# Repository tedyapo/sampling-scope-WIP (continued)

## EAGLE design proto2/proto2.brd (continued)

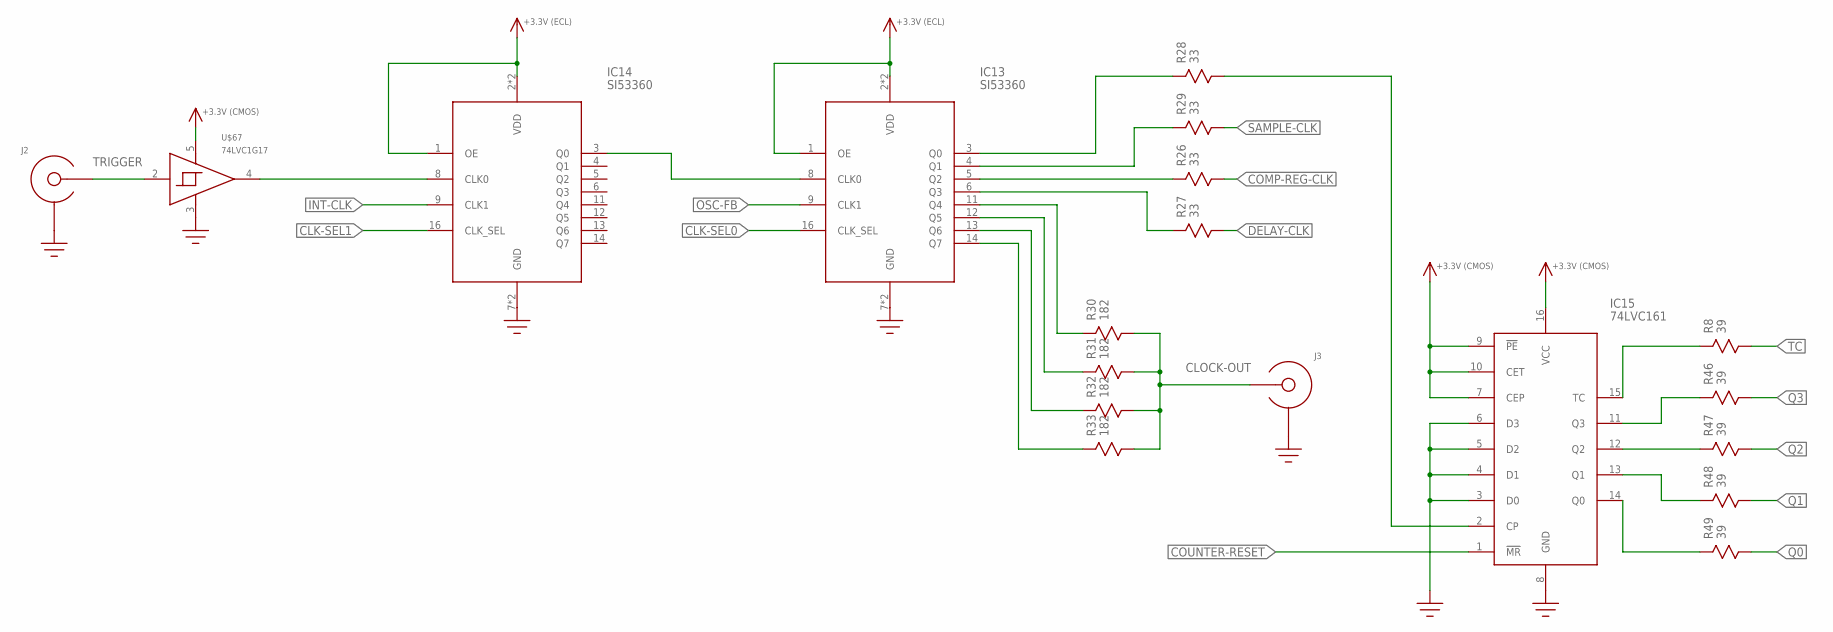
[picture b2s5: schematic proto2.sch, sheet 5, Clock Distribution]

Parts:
IC13, IC14: SI53360; TSSOP16
IC15: 74LVC161; SOIC-16
J2, J3: SMA-EDGE-LAUNCH4L-4020-TAPER-FIXED; SMA_EDGE_LAUNCH_4L_4020_TAPER_FIXED
R8, R46, R47, R48, R49: 39; 0402
R26, R27, R28, R29: 33; R0603
R30, R31, R32, R33: 182; R0603
U$67: 74LVC1G17; SOT23-5

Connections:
CLK-SEL0: IC13.16 (CLK_SEL); also elsewhere on the board
CLK-SEL1: IC14.16 (CLK_SEL); also elsewhere on the board
CLOCK-OUT: J3.CENTER@1 (CENTER), J3.P$3 (CENTER), R30.P$2, R31.P$2, R32.P$2, R33.P$2
COMP-REG-CLK: R26.P$2; also elsewhere on the board
COUNTER-RESET: IC15.1 (!MR!); also elsewhere on the board
DELAY-CLK: R27.P$2; also elsewhere on the board
GND: IC13.7 (GND), IC13.10 (GND), IC14.7 (GND), IC14.10 (GND), IC15.3 (D0), IC15.4 (D1), IC15.5 (D2), IC15.6 (D3), IC15.8 (GND), J2.BOTTOM_GND (SHIELD), J2.GND@1 (SHIELD), J2.GND@2 (SHIELD), J2.GND@3 (SHIELD), J2.GND@4 (SHIELD), J2.GND@5 (SHIELD), J2.GND@6 (SHIELD), J2.GND@7 (SHIELD), J2.GND@8 (SHIELD), J2.GND@14 (SHIELD), J2.GND@15 (SHIELD), J2.GND@16 (SHIELD), J2.GND@17 (SHIELD), J2.GND_PAD1 (SHIELD), J2.GND_PAD2 (SHIELD), J2.P$1 (SHIELD), J2.P$2 (SHIELD), J3.BOTTOM_GND (SHIELD), J3.GND@1 (SHIELD), J3.GND@2 (SHIELD), J3.GND@3 (SHIELD), J3.GND@4 (SHIELD), J3.GND@5 (SHIELD), J3.GND@6 (SHIELD), J3.GND@7 (SHIELD), J3.GND@8 (SHIELD), J3.GND@14 (SHIELD), J3.GND@15 (SHIELD), J3.GND@16 (SHIELD), J3.GND@17 (SHIELD), J3.GND_PAD1 (SHIELD), J3.GND_PAD2 (SHIELD), J3.P$1 (SHIELD), J3.P$2 (SHIELD), U$67.3 (GND); also elsewhere on the board
INT-CLK: IC14.9 (CLK1); also elsewhere on the board
unnamed: IC15.12 (Q2), R47.1
unnamed: IC13.5 (Q2), R26.P$1
unnamed: IC13.6 (Q3), R27.P$1
unnamed: IC13.4 (Q1), R29.P$1
unnamed: IC14.8 (CLK0), U$67.4 (OUT)
unnamed: IC13.8 (CLK0), IC14.3 (Q0)
unnamed: IC13.3 (Q0), R28.P$1
unnamed: IC15.2 (CP), R28.P$2
unnamed: IC13.11 (Q4), R30.P$1
unnamed: IC13.12 (Q5), R31.P$1
unnamed: IC13.13 (Q6), R32.P$1
unnamed: IC13.14 (Q7), R33.P$1
unnamed: IC15.11 (Q3), R46.1
unnamed: IC15.15 (TC), R8.1
unnamed: IC15.13 (Q1), R48.1
unnamed: IC15.14 (Q0), R49.1
OSC-FB: IC13.9 (CLK1); also elsewhere on the board
Q0: R49.2; also elsewhere on the board
Q1: R48.2; also elsewhere on the board
Q2: R47.2; also elsewhere on the board
Q3: R46.2; also elsewhere on the board
SAMPLE-CLK: R29.P$2; also elsewhere on the board
TC: R8.2; also elsewhere on the board
TRIGGER: J2.CENTER@1 (CENTER), J2.P$3 (CENTER), U$67.2 (IN)
VCC1: IC13.1 (OE), IC13.2 (VDD), IC13.15 (VDD), IC14.1 (OE), IC14.2 (VDD), IC14.15 (VDD); also elsewhere on the board
VCC2: IC15.7 (CEP), IC15.9 (!PE!), IC15.10 (CET), IC15.16 (VCC), U$67.5 (VCC); also elsewhere on the board

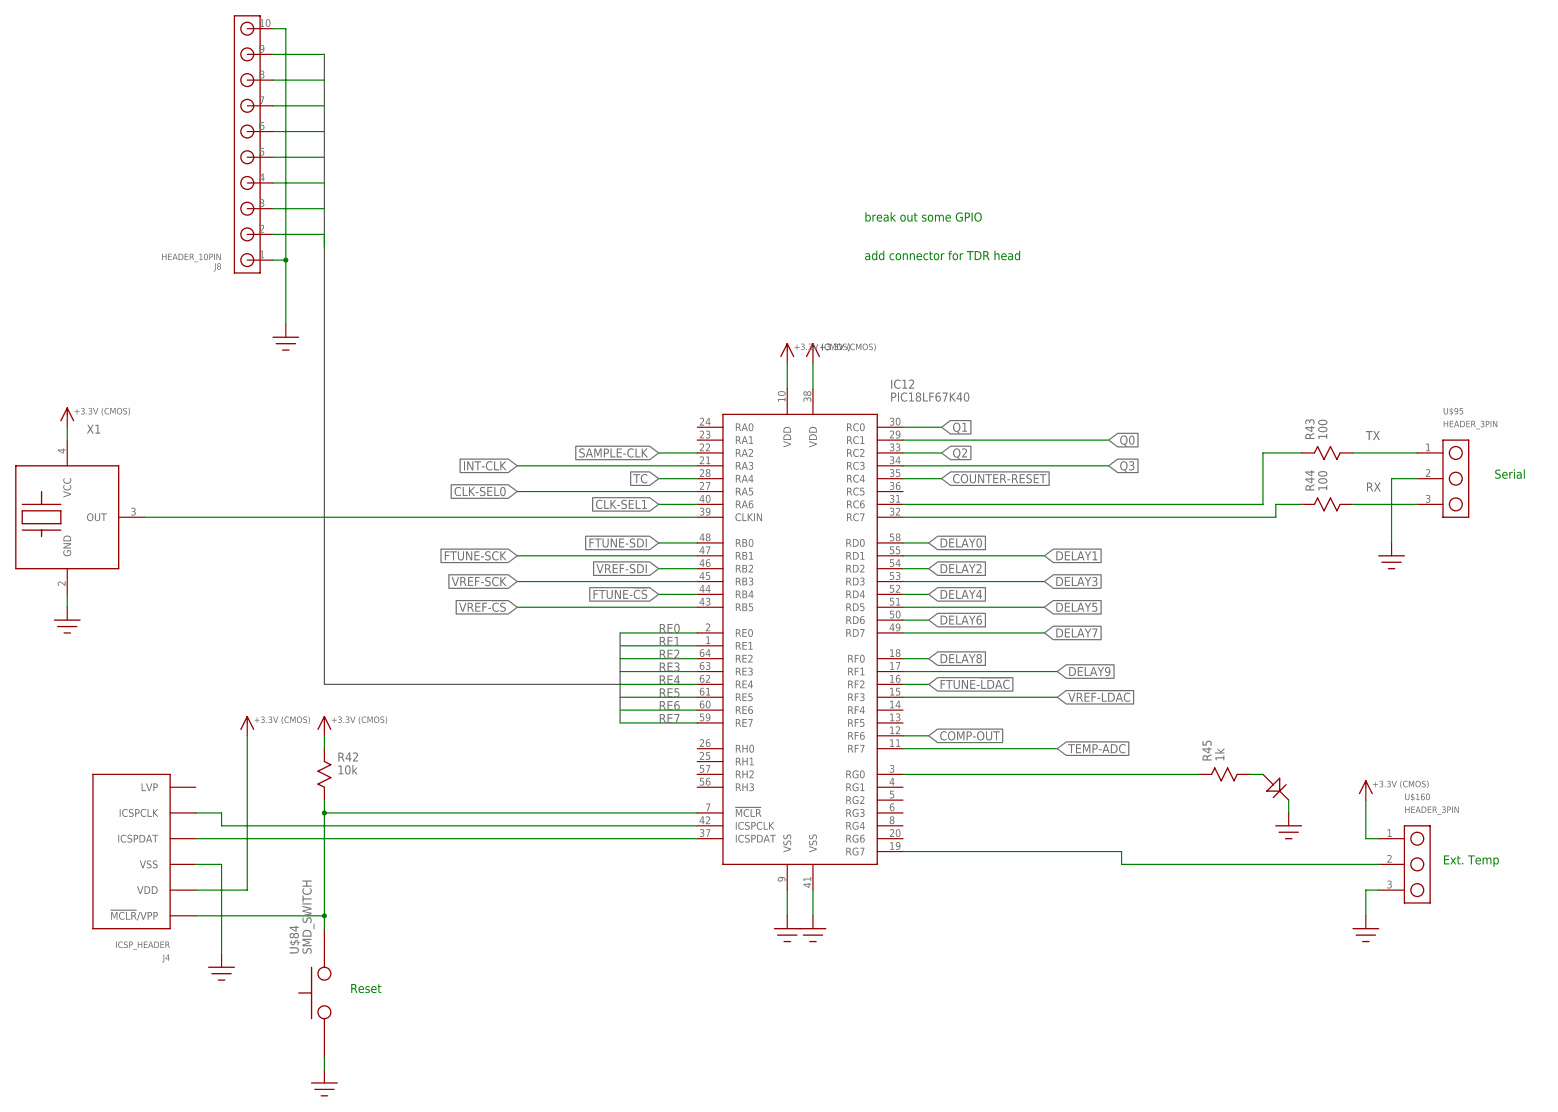
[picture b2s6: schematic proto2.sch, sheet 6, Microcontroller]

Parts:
IC12: PIC18LF67K40; TQFP-100-10X10
J4: ICSP_HEADER; HEADER_6PIN
J8: HEADER_10PIN
R42: 10k; R0603
R43, R44: 100; R0603
R45: 1k; R0603
U$84: SMD_SWITCH
U$95, U$160: HEADER_3PIN
U$97: LED_0603
X1: XTAL_OSC; XTAL_3.2X5

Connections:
CLK-SEL0: IC12.27 (RA5); also elsewhere on the board
CLK-SEL1: IC12.40 (RA6); also elsewhere on the board
COMP-OUT: IC12.12 (RF6); also elsewhere on the board
COUNTER-RESET: IC12.35 (RC4); also elsewhere on the board
DELAY0: IC12.58 (RD0); also elsewhere on the board
DELAY1: IC12.55 (RD1); also elsewhere on the board
DELAY2: IC12.54 (RD2); also elsewhere on the board
DELAY3: IC12.53 (RD3); also elsewhere on the board
DELAY4: IC12.52 (RD4); also elsewhere on the board
DELAY5: IC12.51 (RD5); also elsewhere on the board
DELAY6: IC12.50 (RD6); also elsewhere on the board
DELAY7: IC12.49 (RD7); also elsewhere on the board
DELAY8: IC12.18 (RF0); also elsewhere on the board
DELAY9: IC12.17 (RF1); also elsewhere on the board
FTUNE-!CS!: IC12.44 (RB4); also elsewhere on the board
FTUNE-!LDAC!: IC12.16 (RF2); also elsewhere on the board
FTUNE-SCK: IC12.47 (RB1); also elsewhere on the board
FTUNE-SDI: IC12.48 (RB0); also elsewhere on the board
GND: IC12.9 (VSS), IC12.41 (VSS), J4.3 (VSS), J8.1, J8.10, U$84.P$1, U$84.P$2, U$95.2, U$97.C, U$160.3, X1.2 (GND); also elsewhere on the board
INT-CLK: IC12.21 (RA3); also elsewhere on the board
unnamed: IC12.7 (!MCLR!), J4.1 (!MCLR!/VPP), R42.P$2, U$84.P$3, U$84.P$4
unnamed: IC12.37 (ICSPDAT), J4.4 (ICSPDAT)
unnamed: IC12.42 (ICSPCLK), J4.5 (ICSPCLK)
unnamed: R45.P$2, U$97.A
unnamed: IC12.39 (CLKIN), X1.3 (OUT)
unnamed: IC12.32 (RC7), R44.P$1
unnamed: IC12.31 (RC6), R43.P$1
unnamed: IC12.3 (RG0), R45.P$1
unnamed: IC12.19 (RG7), U$160.2
Q0: IC12.29 (RC1); also elsewhere on the board
Q1: IC12.30 (RC0); also elsewhere on the board
Q2: IC12.33 (RC2); also elsewhere on the board
Q3: IC12.34 (RC3); also elsewhere on the board
RE0: IC12.2 (RE0), J8.9
RE1: IC12.1 (RE1), J8.8
RE2: IC12.64 (RE2), J8.7
RE3: IC12.63 (RE3), J8.6
RE4: IC12.62 (RE4), J8.5
RE5: IC12.61 (RE5), J8.4
RE6: IC12.60 (RE6), J8.3
RE7: IC12.59 (RE7), J8.2
RX: R44.P$2, U$95.3
SAMPLE-CLK: IC12.22 (RA2); also elsewhere on the board
TC: IC12.28 (RA4); also elsewhere on the board
TEMP-ADC: IC12.11 (RF7); also elsewhere on the board
TX: R43.P$2, U$95.1
VCC2: IC12.10 (VDD), IC12.38 (VDD), J4.2 (VDD), R42.P$1, U$160.1, X1.4 (VCC); also elsewhere on the board
VREF-!CS!: IC12.43 (RB5); also elsewhere on the board
VREF-!LDAC!: IC12.15 (RF3); also elsewhere on the board
VREF-SCK: IC12.45 (RB3); also elsewhere on the board
VREF-SDI: IC12.46 (RB2); also elsewhere on the board

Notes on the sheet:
break out some GPIO
add connector for TDR head
Serial
Ext. Temp
Reset

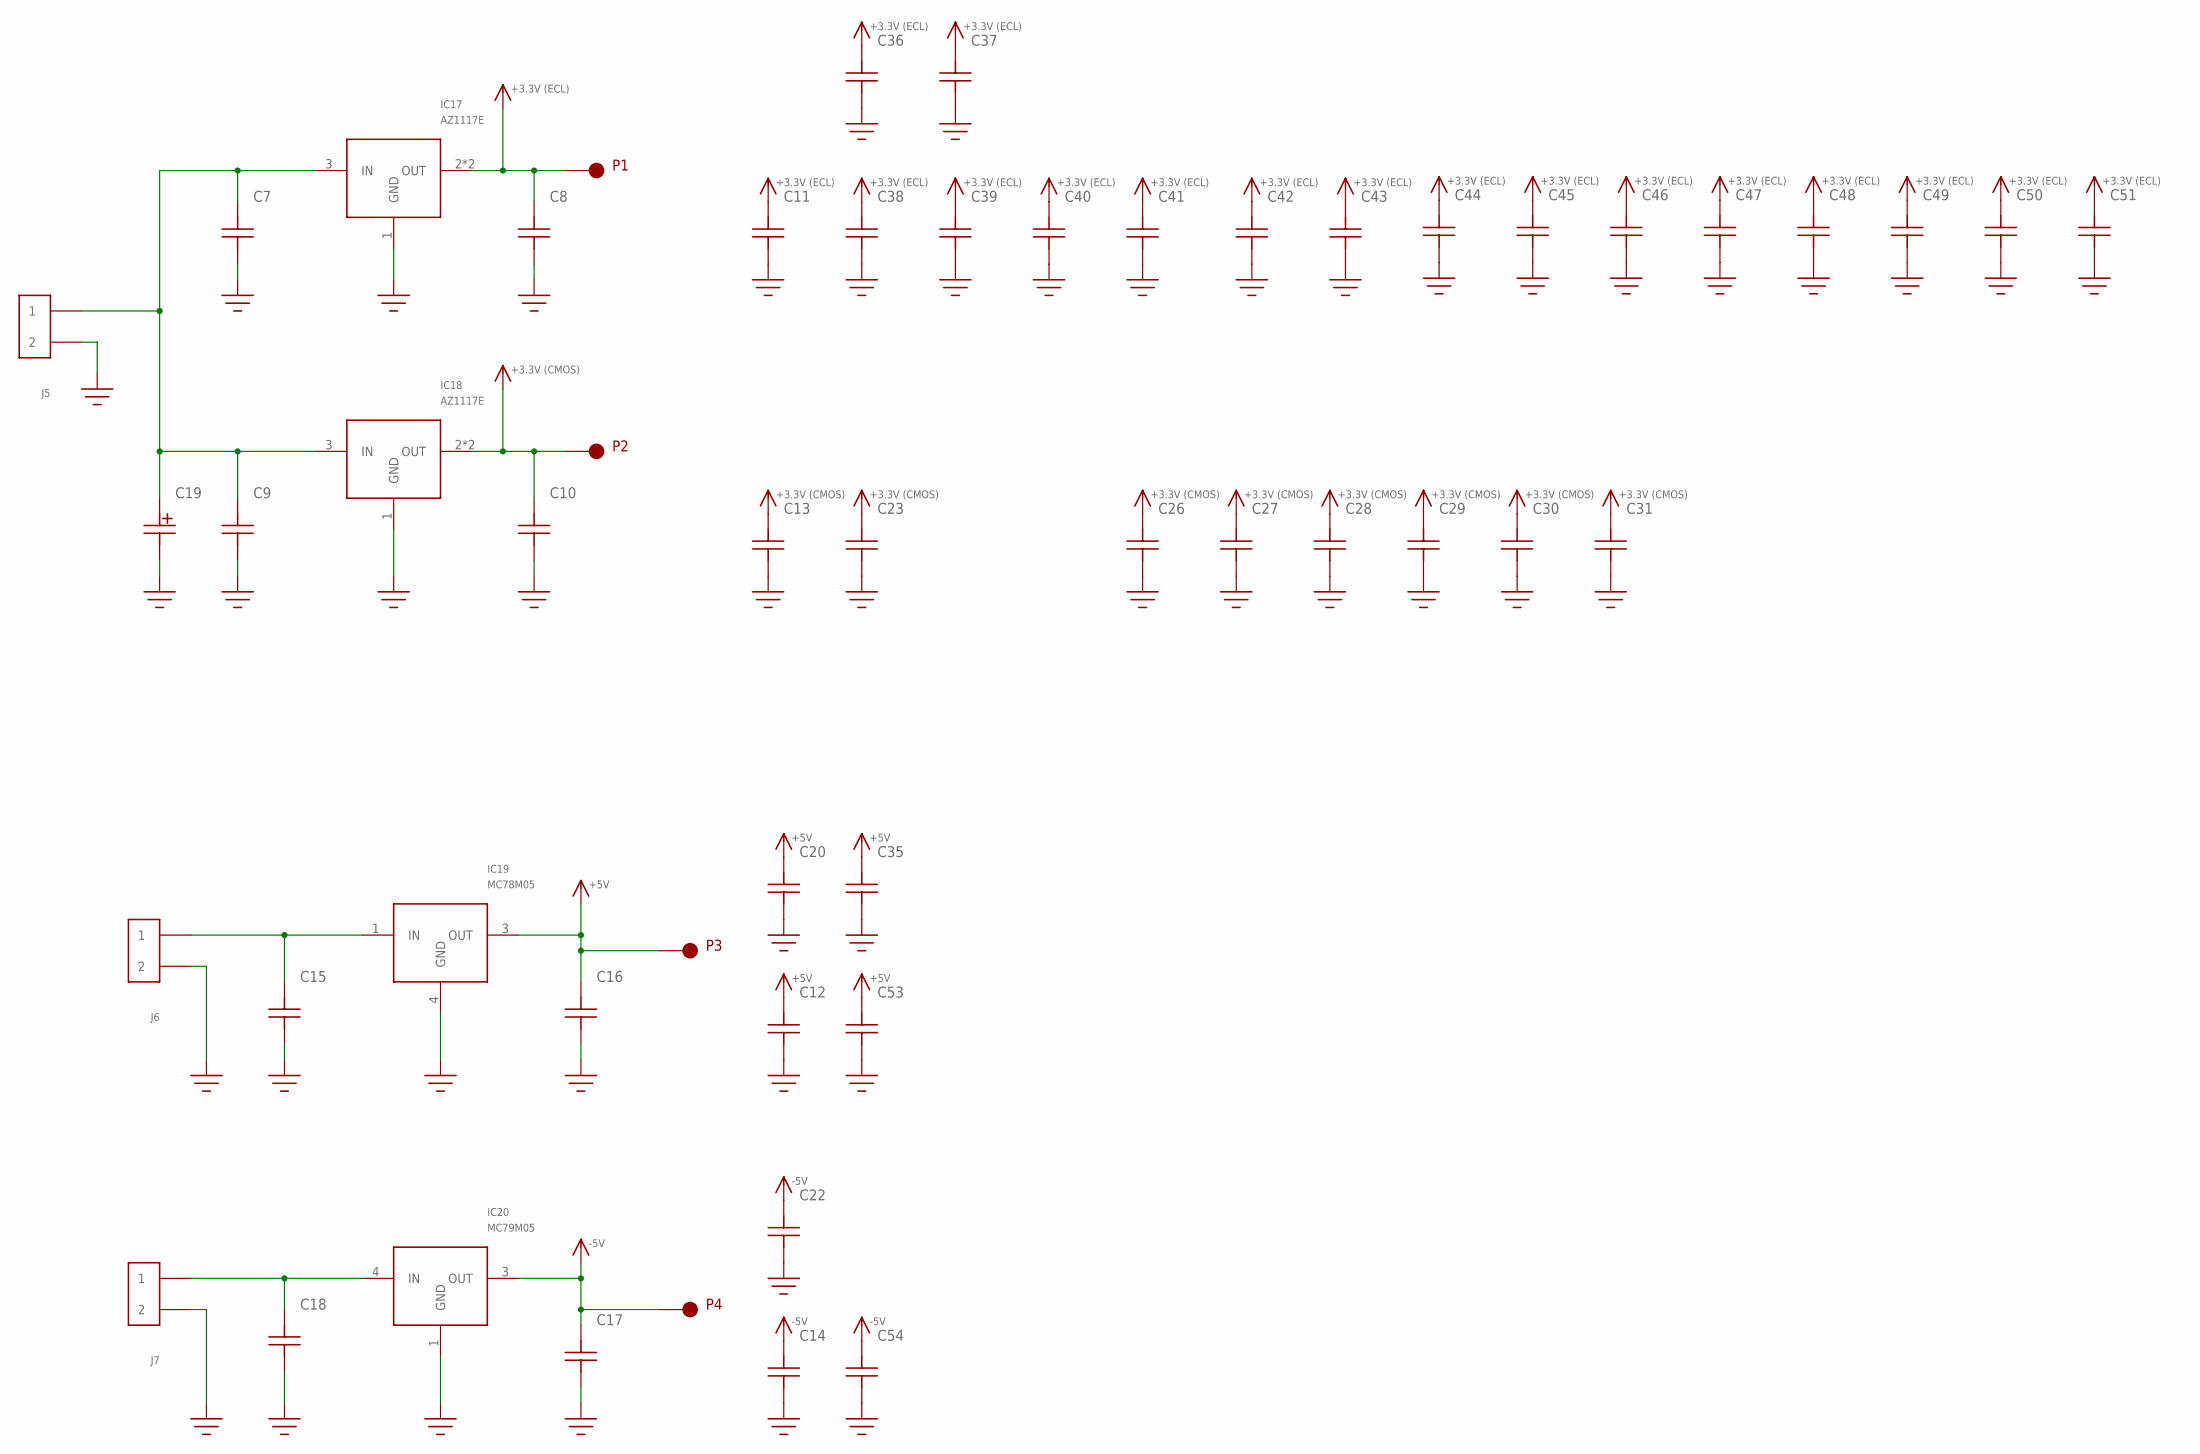
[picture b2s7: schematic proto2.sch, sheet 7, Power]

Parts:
C7, C8, C9, C10, C15, C16, C17, C18: C1206; 1206
C11, C12, C13, C14, C23, C26, C27, C28, C29, C30, C31, C38, C39, C40, C41, C42, C43, C44, C45, C46, C47, C48, C49, C50, C51, C53, C54: C0603
C19: C-POLARIZED; CAP-E61
C20, C22, C35, C36, C37: C; C0402
IC17, IC18: AZ1117E; SOT-223
IC19: MC78M05; DPAK
IC20: MC79M05; DPAK
J5, J6, J7: HEADER_2PINSCREW-TERM; FCI_20020316_SCREW_TERM_2P
P1, P2, P3, P4: ICSP_PAD

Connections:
+5V: C12.P$2, C16.P$2, C20.2, C35.2, C53.P$2, IC19.3 (OUT), P3.P$1; also elsewhere on the board
-5V: C14.P$2, C17.P$2, C22.2, C54.P$2, IC20.3 (OUT), P4.P$1; also elsewhere on the board
GND: C7.P$1, C8.P$1, C9.P$1, C10.P$1, C11.P$1, C12.P$1, C13.P$1, C14.P$1, C15.P$1, C16.P$1, C17.P$1, C18.P$1, C19.-, C20.1, C22.1, C23.P$1, C26.P$1, C27.P$1, C28.P$1, C29.P$1, C30.P$1, C31.P$1, C35.1, C36.1, C37.1, C38.P$1, C39.P$1, C40.P$1, C41.P$1, C42.P$1, C43.P$1, C44.P$1, C45.P$1, C46.P$1, C47.P$1, C48.P$1, C49.P$1, C50.P$1, C51.P$1, C53.P$1, C54.P$1, IC17.1 (GND), IC18.1 (GND), IC19.4 (GND), IC20.1 (GND), J5.P$2 (2), J6.P$2 (2), J7.P$2 (2); also elsewhere on the board
unnamed: C7.P$2, C9.P$2, C19.+, IC17.3 (IN), IC18.3 (IN), J5.P$1 (1)
unnamed: C15.P$2, IC19.1 (IN), J6.P$1 (1)
unnamed: C18.P$2, IC20.4 (IN), J7.P$1 (1)
VCC1: C8.P$2, C11.P$2, C36.2, C37.2, C38.P$2, C39.P$2, C40.P$2, C41.P$2, C42.P$2, C43.P$2, C44.P$2, C45.P$2, C46.P$2, C47.P$2, C48.P$2, C49.P$2, C50.P$2, C51.P$2, IC17.2 (OUT), IC17.4 (OUT), P1.P$1; also elsewhere on the board
VCC2: C10.P$2, C13.P$2, C23.P$2, C26.P$2, C27.P$2, C28.P$2, C29.P$2, C30.P$2, C31.P$2, IC18.2 (OUT), IC18.4 (OUT), P2.P$1; also elsewhere on the board

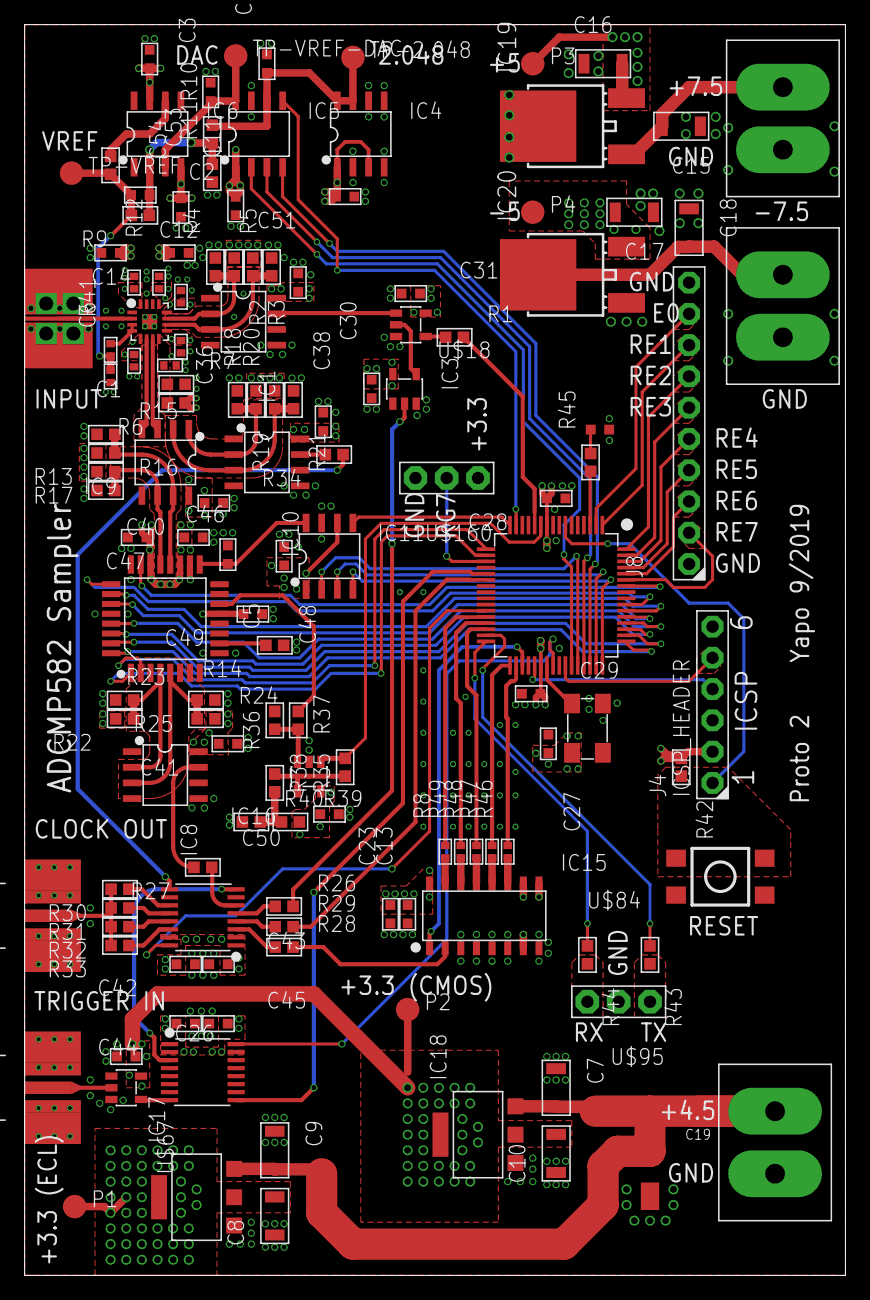
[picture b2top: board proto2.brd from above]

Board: 4 copper layers, 66.7 x 101.6 mm, 138 parts (0 on the bottom side), 106 nets.

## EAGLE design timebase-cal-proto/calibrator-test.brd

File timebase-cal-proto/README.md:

# timebase-calibrator

This design is a simple test of the timebase calibration loop.

It does not function as an oscilloscope, simply serving to test calibration strategies for the SY89296U-based timebase.

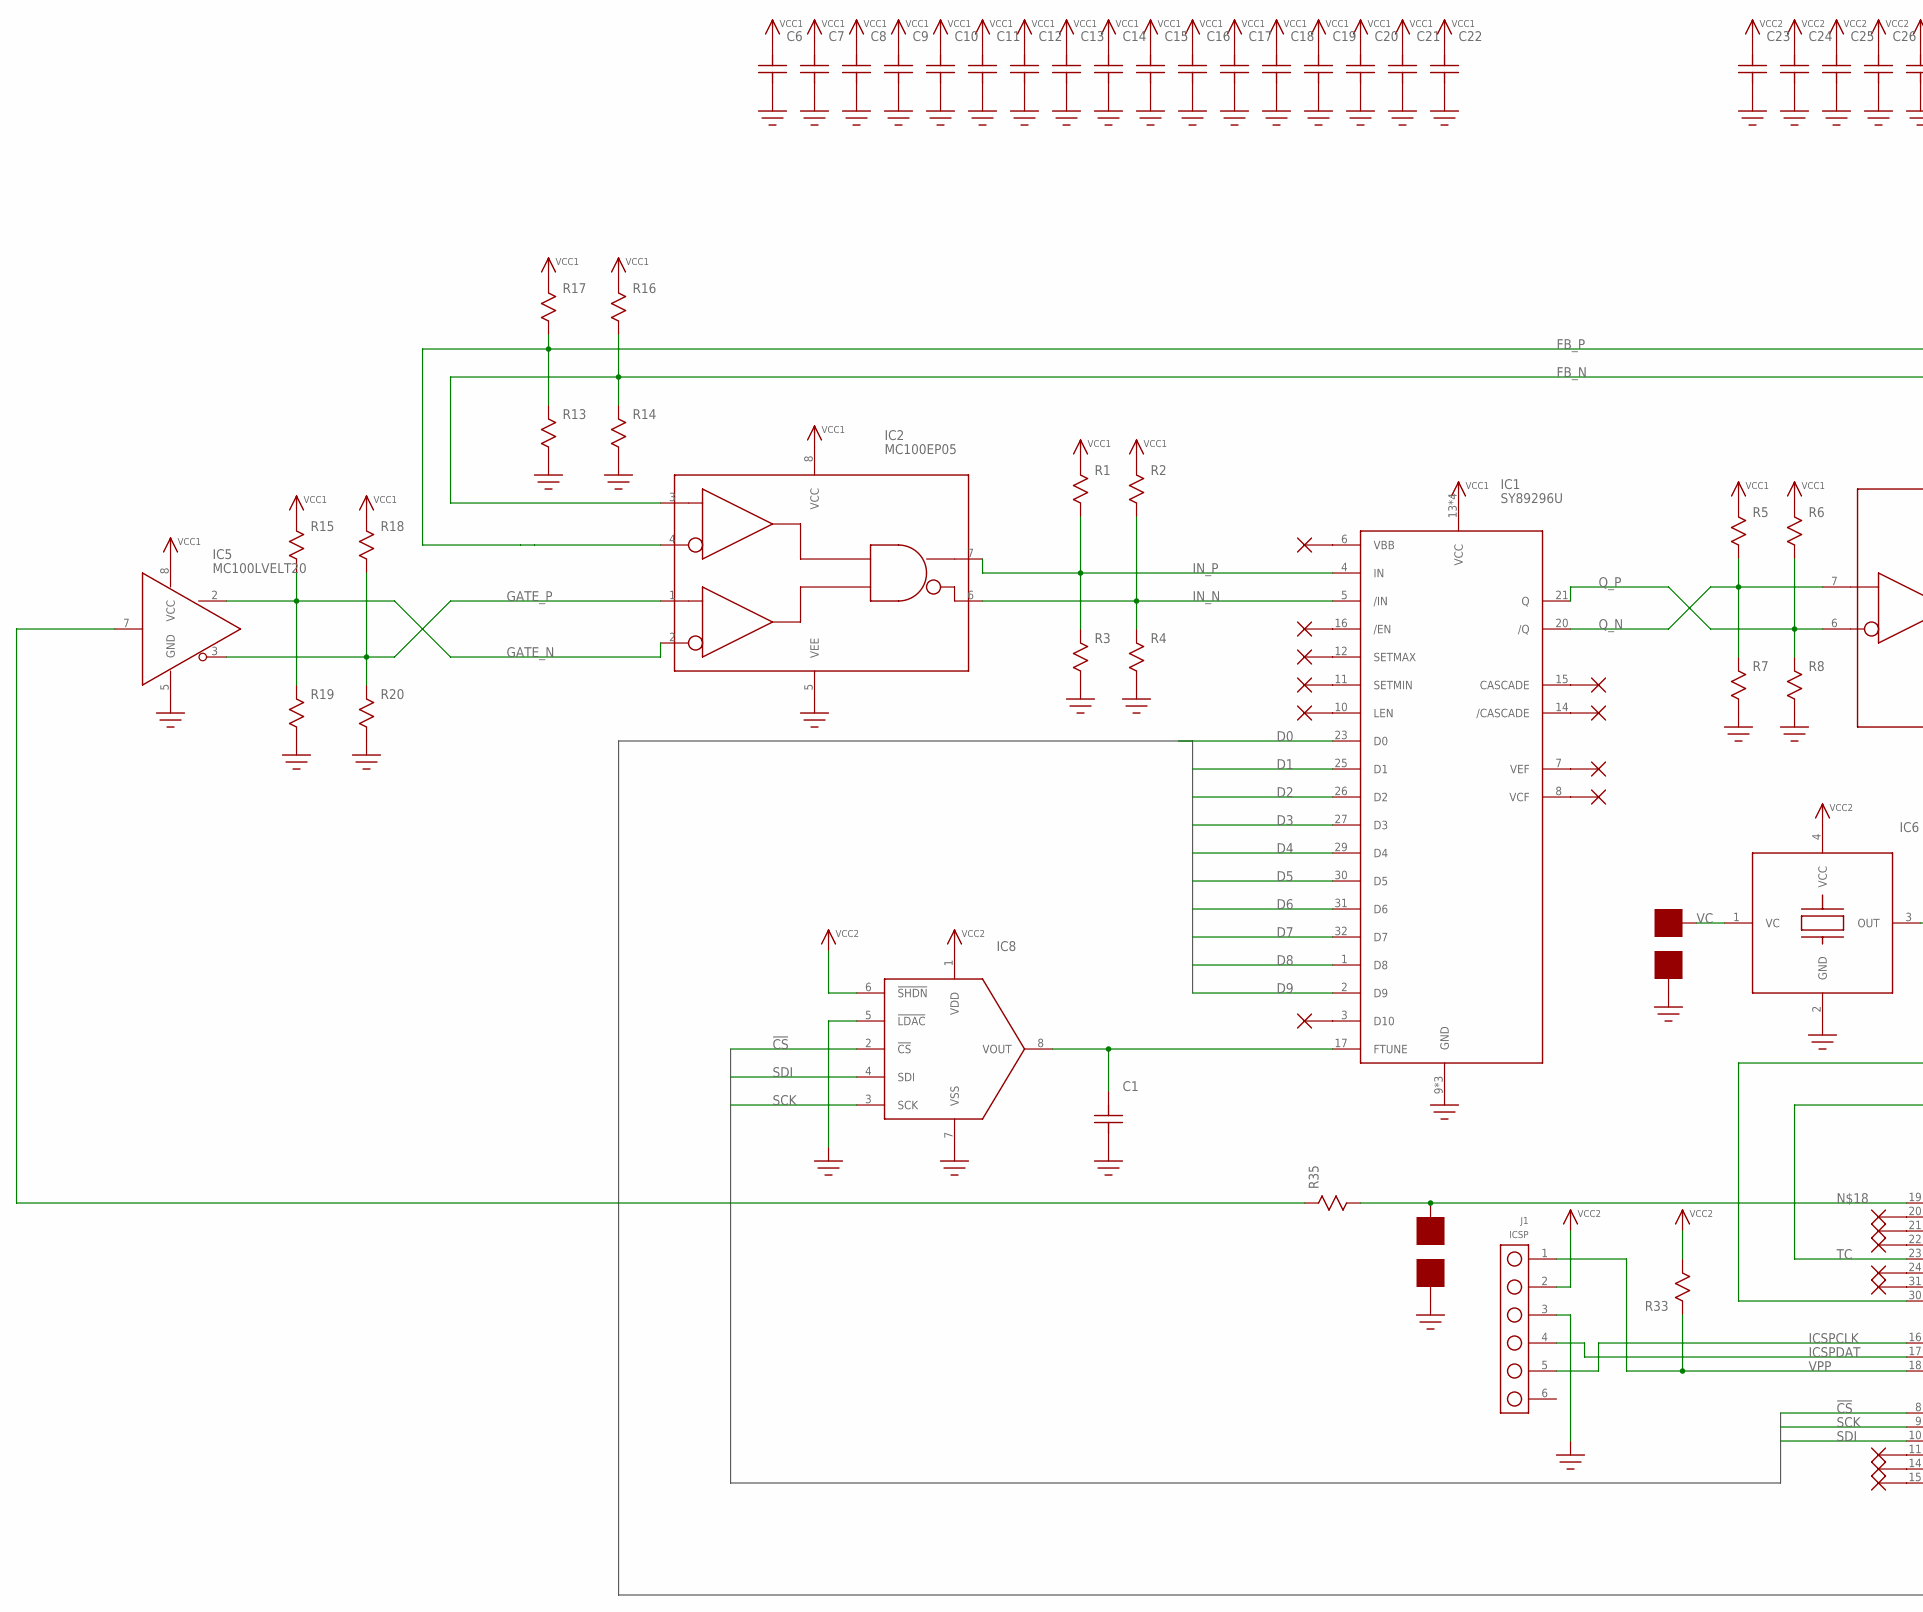
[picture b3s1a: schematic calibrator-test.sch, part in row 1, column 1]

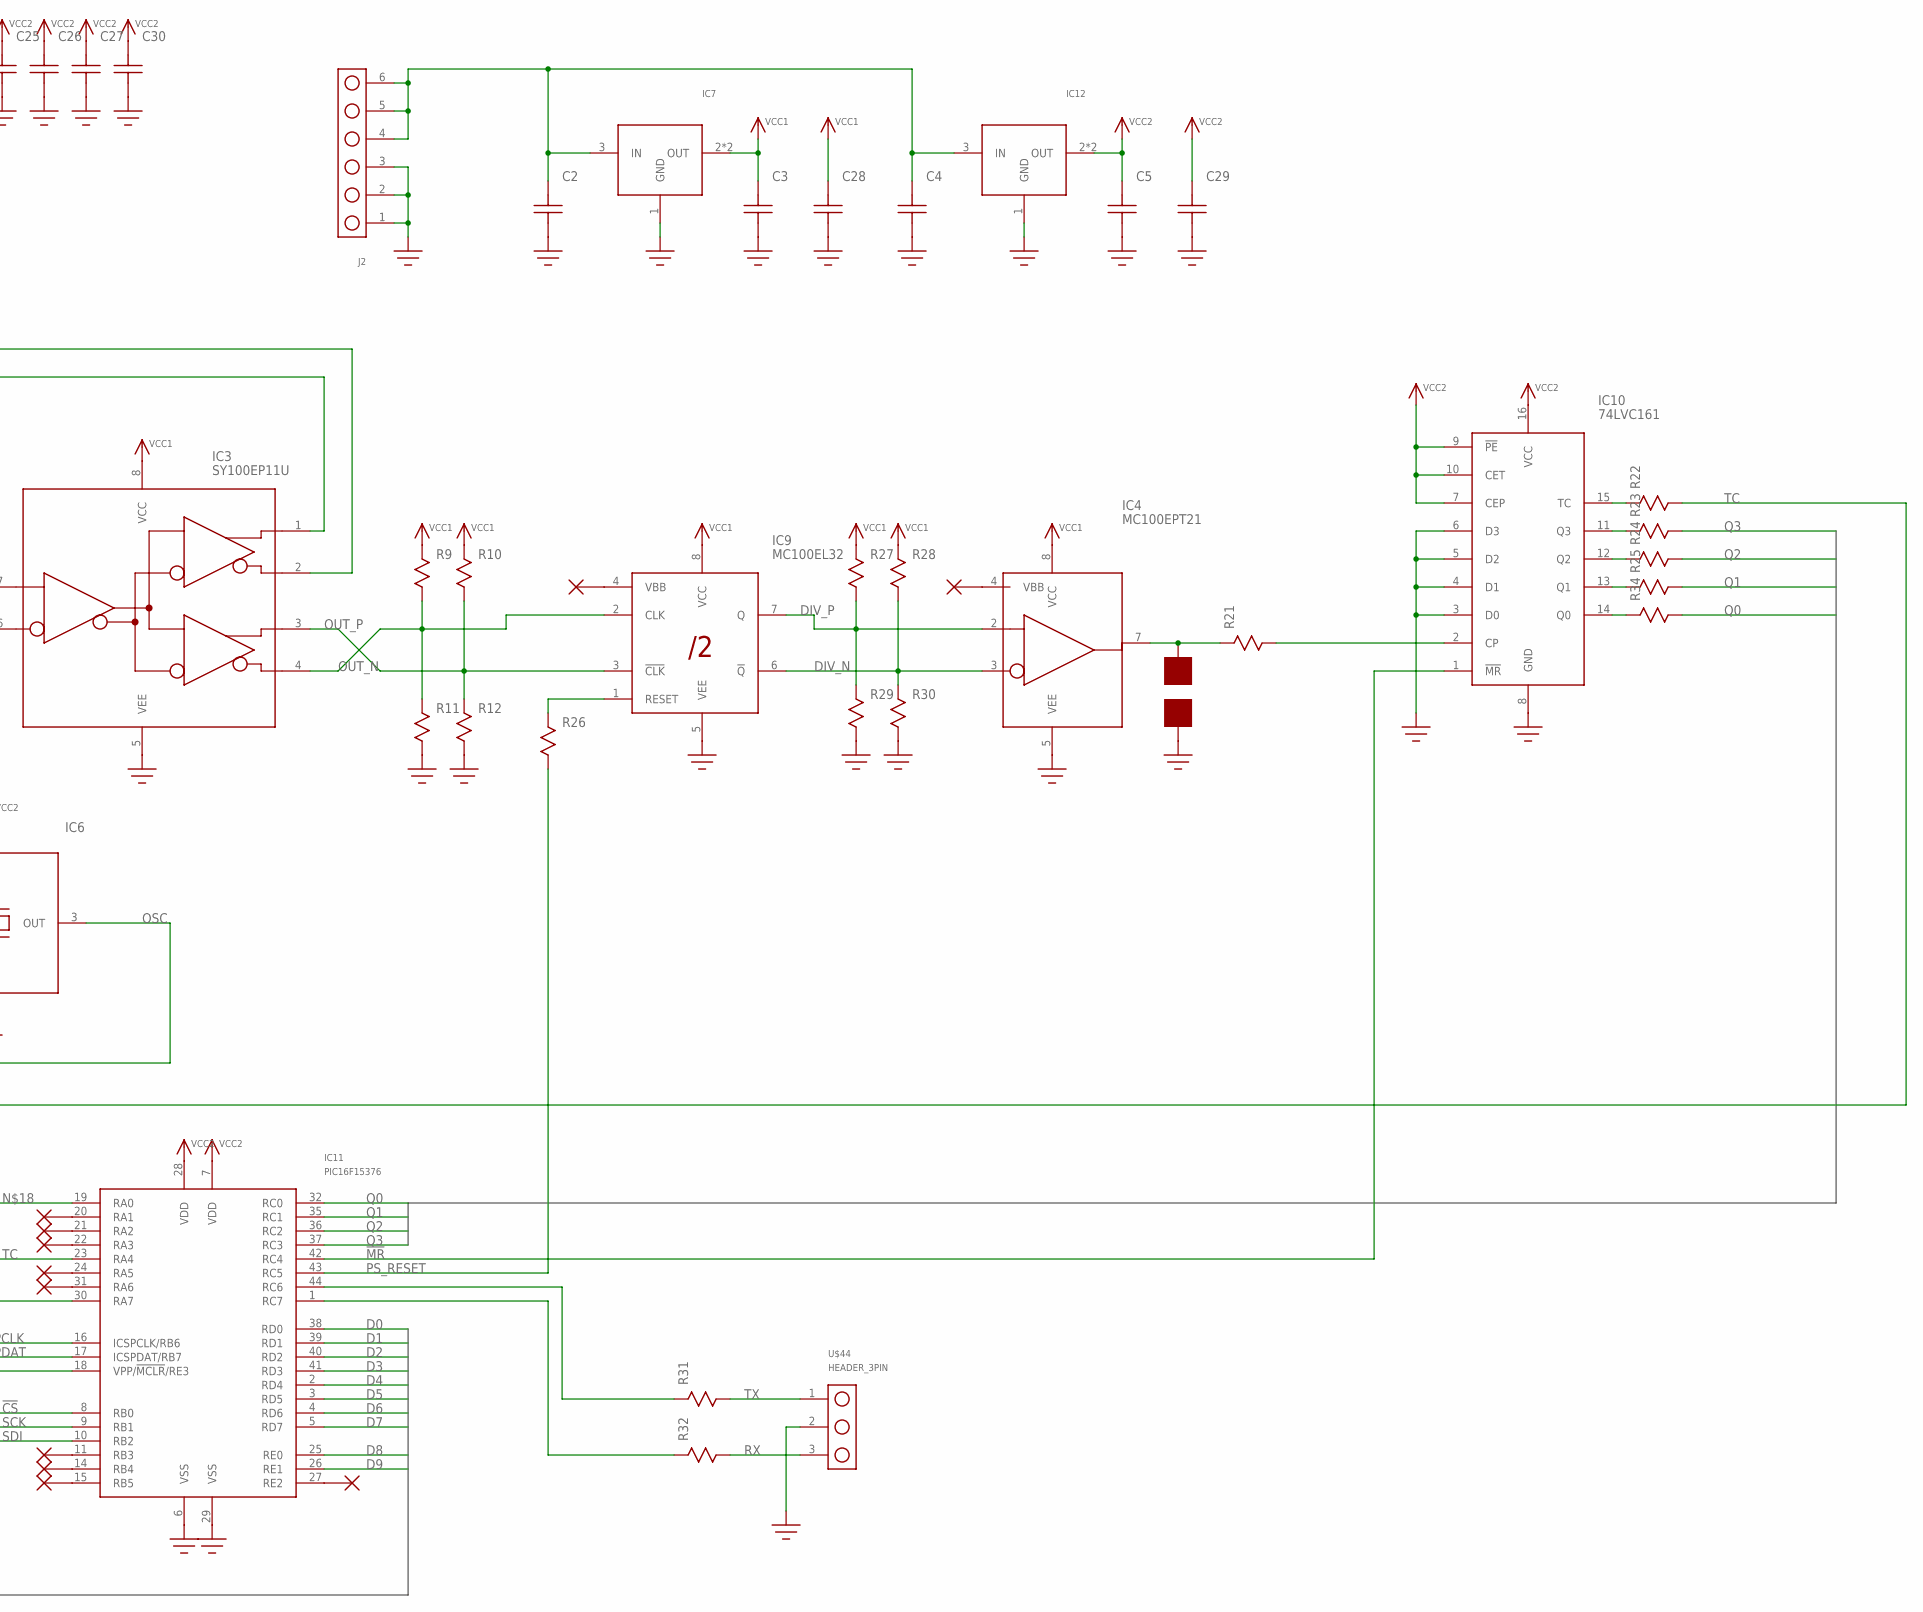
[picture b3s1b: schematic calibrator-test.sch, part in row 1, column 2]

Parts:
C1, C6, C7, C8, C9, C10, C11, C12, C13, C14, C15, C16, C17, C18, C19, C20, C21, C22, C23, C24, C25, C26, C27, C30: C0603
C2, C3, C4, C5, C28, C29: C1206; 1206
IC1: SY89296U; TQFP32_7X7
IC2: MC100EP05; SOIC8
IC3: SY100EP11U; SOIC8
IC4: MC100EPT21; SOIC8
IC5: MC100LVELT20; SOIC8
IC6: XTAL_OSC_VC; XTAL_3.2X5
IC7, IC12: AZ1117E; SOT-223
IC8: MCP48X1; SOIC8
IC9: MC100EL32; SOIC8
IC10: 74LVC161; SOIC-16
IC11: PIC16F15376; TQFP44
J1: ICSP; HEADER_6PIN
J2: HEADER_6PIN
R1, R2, R3, R4, R5, R6, R7, R8, R9, R10, R11, R12, R13, R14, R15, R16, R17, R18, R19, R20, R21, R22, R23, R24, R25, R26, R27, R28, R29, R30, R31, R32, R33, R34, R35: R0603
U$44: HEADER_3PIN
U$48, U$75, U$76, U$77, U$78, U$81: PAD50MIL; PAD_50MIL

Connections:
!CS!: IC8.2 (!CS!), IC11.8 (RB0)
!GATE!: IC5.7 (D), R35.P$1
!MR!: IC10.1 (!MR!), IC11.42 (RC4)
D0: IC1.23 (D0), IC11.38 (RD0)
D1: IC1.25 (D1), IC11.39 (RD1)
D2: IC1.26 (D2), IC11.40 (RD2)
D3: IC1.27 (D3), IC11.41 (RD3)
D4: IC1.29 (D4), IC11.2 (RD4)
D5: IC1.30 (D5), IC11.3 (RD5)
D6: IC1.31 (D6), IC11.4 (RD6)
D7: IC1.32 (D7), IC11.5 (RD7)
D8: IC1.1 (D8), IC11.25 (RE0)
D9: IC1.2 (D9), IC11.26 (RE1)
DIV_N: IC4.3 (!D!), IC9.6 (!Q!), R28.P$2, R30.P$1
DIV_P: IC4.2 (D), IC9.7 (Q), R27.P$2, R29.P$1
FB_N: IC2.3 (D1), IC3.1 (Q0), R14.P$1, R16.P$2
FB_P: IC2.4 (!D1!), IC3.2 (!Q0!), R13.P$1, R17.P$2
GATE_N: IC2.2 (!D0!), IC5.2 (Q), R15.P$2, R19.P$1
GATE_P: IC2.1 (D0), IC5.3 (!Q!), R18.P$2, R20.P$1
GND: C1.P$1, C2.P$1, C3.P$1, C4.P$1, C5.P$1, C6.P$1, C7.P$1, C8.P$1, C9.P$1, C10.P$1, C11.P$1, C12.P$1, C13.P$1, C14.P$1, C15.P$1, C16.P$1, C17.P$1, C18.P$1, C19.P$1, C20.P$1, C21.P$1, C22.P$1, C23.P$1, C24.P$1, C25.P$1, C26.P$1, C27.P$1, C28.P$1, C29.P$1, C30.P$1, IC1.9 (GND), IC1.24 (GND), IC1.28 (GND), IC2.5 (VEE), IC3.5 (VEE), IC4.5 (VEE), IC5.5 (GND), IC6.2 (GND), IC7.1 (GND), IC8.5 (!LDAC!), IC8.7 (VSS), IC9.5 (VEE), IC10.3 (D0), IC10.4 (D1), IC10.5 (D2), IC10.6 (D3), IC10.8 (GND), IC11.6 (VSS), IC11.29 (VSS), IC12.1 (GND), J1.3, J2.1, J2.2, J2.3, R3.P$2, R4.P$2, R7.P$2, R8.P$2, R11.P$2, R12.P$2, R13.P$2, R14.P$2, R19.P$2, R20.P$2, R29.P$2, R30.P$2, U$44.2, U$76.P$1, U$78.P$1, U$81.P$1
ICSPCLK: IC11.16 (ICSPCLK/RB6), J1.5
ICSPDAT: IC11.17 (ICSPDAT/RB7), J1.4
IN_N: IC1.5 (/IN), IC2.6 (!Q!), R2.P$2, R4.P$1
IN_P: IC1.4 (IN), IC2.7 (Q), R1.P$2, R3.P$1
unnamed: IC10.2 (CP), R21.P$2
unnamed: IC10.15 (TC), R22.P$1
unnamed: IC10.11 (Q3), R23.P$1
unnamed: IC10.12 (Q2), R24.P$1
unnamed: IC10.13 (Q1), R25.P$1
unnamed: IC10.14 (Q0), R34.P$1
unnamed: IC11.19 (RA0), R35.P$2, U$75.P$1
unnamed: IC11.44 (RC6), R31.P$1
unnamed: IC11.1 (RC7), R32.P$1
unnamed: C2.P$2, C4.P$2, IC7.3 (IN), IC12.3 (IN), J2.4, J2.5, J2.6
unnamed: C1.P$2, IC1.17 (FTUNE), IC8.8 (VOUT)
unnamed: IC9.1 (RESET), R26.P$1
unnamed: IC4.7 (Q), R21.P$1, U$77.P$1
OSC: IC6.3 (OUT), IC11.30 (RA7)
OUT_N: IC3.4 (!Q1!), IC9.2 (CLK), R9.P$2, R11.P$1
OUT_P: IC3.3 (Q1), IC9.3 (!CLK!), R10.P$2, R12.P$1
PS_RESET: IC11.43 (RC5), R26.P$2
Q0: IC11.32 (RC0), R34.P$2
Q1: IC11.35 (RC1), R25.P$2
Q2: IC11.36 (RC2), R24.P$2
Q3: IC11.37 (RC3), R23.P$2
Q_N: IC1.20 (/Q), IC3.7 (D), R5.P$2, R7.P$1
Q_P: IC1.21 (Q), IC3.6 (!D!), R6.P$2, R8.P$1
RX: R32.P$2, U$44.3
SCK: IC8.3 (SCK), IC11.9 (RB1)
SDI: IC8.4 (SDI), IC11.10 (RB2)
TC: IC11.23 (RA4), R22.P$2
TX: R31.P$2, U$44.1
VC: IC6.1 (VC), U$48.P$1
VCC1: C3.P$2, C6.P$2, C7.P$2, C8.P$2, C9.P$2, C10.P$2, C11.P$2, C12.P$2, C13.P$2, C14.P$2, C15.P$2, C16.P$2, C17.P$2, C18.P$2, C19.P$2, C20.P$2, C21.P$2, C22.P$2, C28.P$2, IC1.13 (VCC), IC1.18 (VCC), IC1.19 (VCC), IC1.22 (VCC), IC2.8 (VCC), IC3.8 (VCC), IC4.8 (VCC), IC5.8 (VCC), IC7.2 (OUT), IC7.4 (OUT), IC9.8 (VCC), R1.P$1, R2.P$1, R5.P$1, R6.P$1, R9.P$1, R10.P$1, R15.P$1, R16.P$1, R17.P$1, R18.P$1, R27.P$1, R28.P$1
VCC2: C5.P$2, C23.P$2, C24.P$2, C25.P$2, C26.P$2, C27.P$2, C29.P$2, C30.P$2, IC6.4 (VCC), IC8.1 (VDD), IC8.6 (!SHDN!), IC10.7 (CEP), IC10.9 (!PE!), IC10.10 (CET), IC10.16 (VCC), IC11.7 (VDD), IC11.28 (VDD), IC12.2 (OUT), IC12.4 (OUT), J1.2, R33.P$2
VPP: IC11.18 (VPP/!MCLR!/RE3), J1.1, R33.P$1

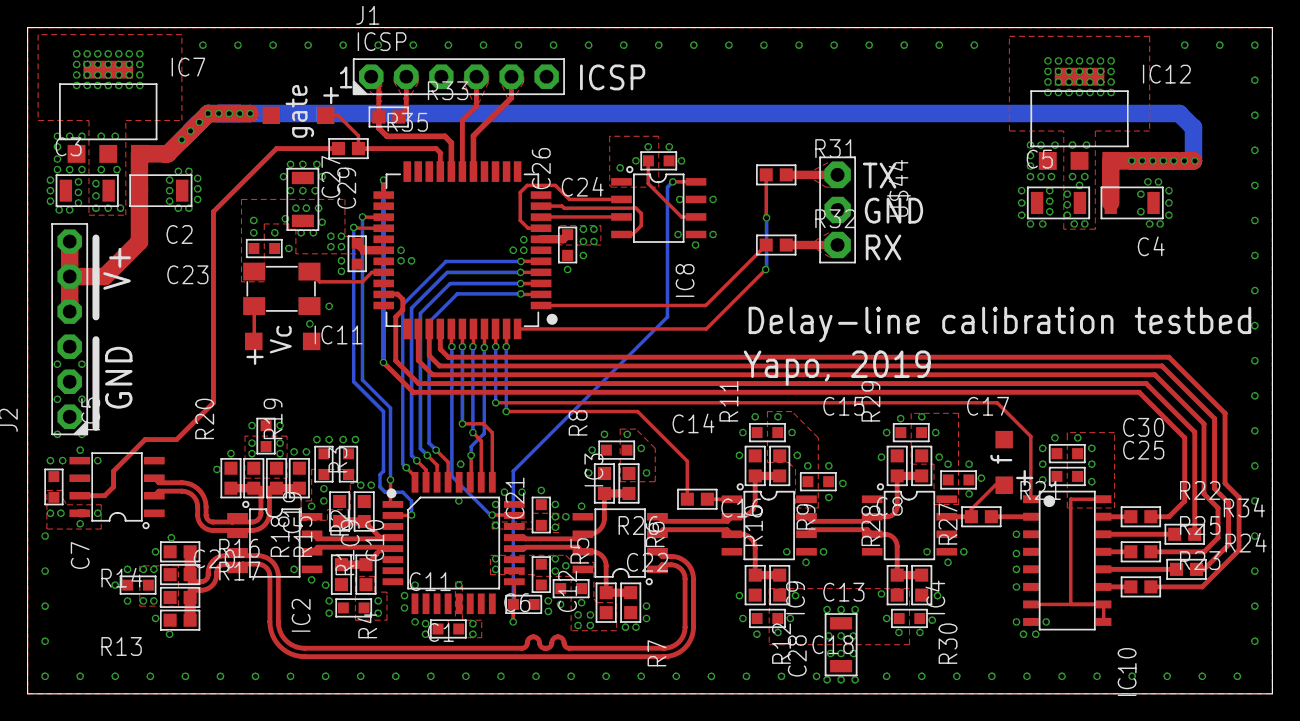
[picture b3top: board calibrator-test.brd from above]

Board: 4 copper layers, 90.2 x 48.3 mm, 86 parts (0 on the bottom side), 56 nets.

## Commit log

2019-10-04 initial release
2019-12-12 proto2 schematic PDF properly formatted
